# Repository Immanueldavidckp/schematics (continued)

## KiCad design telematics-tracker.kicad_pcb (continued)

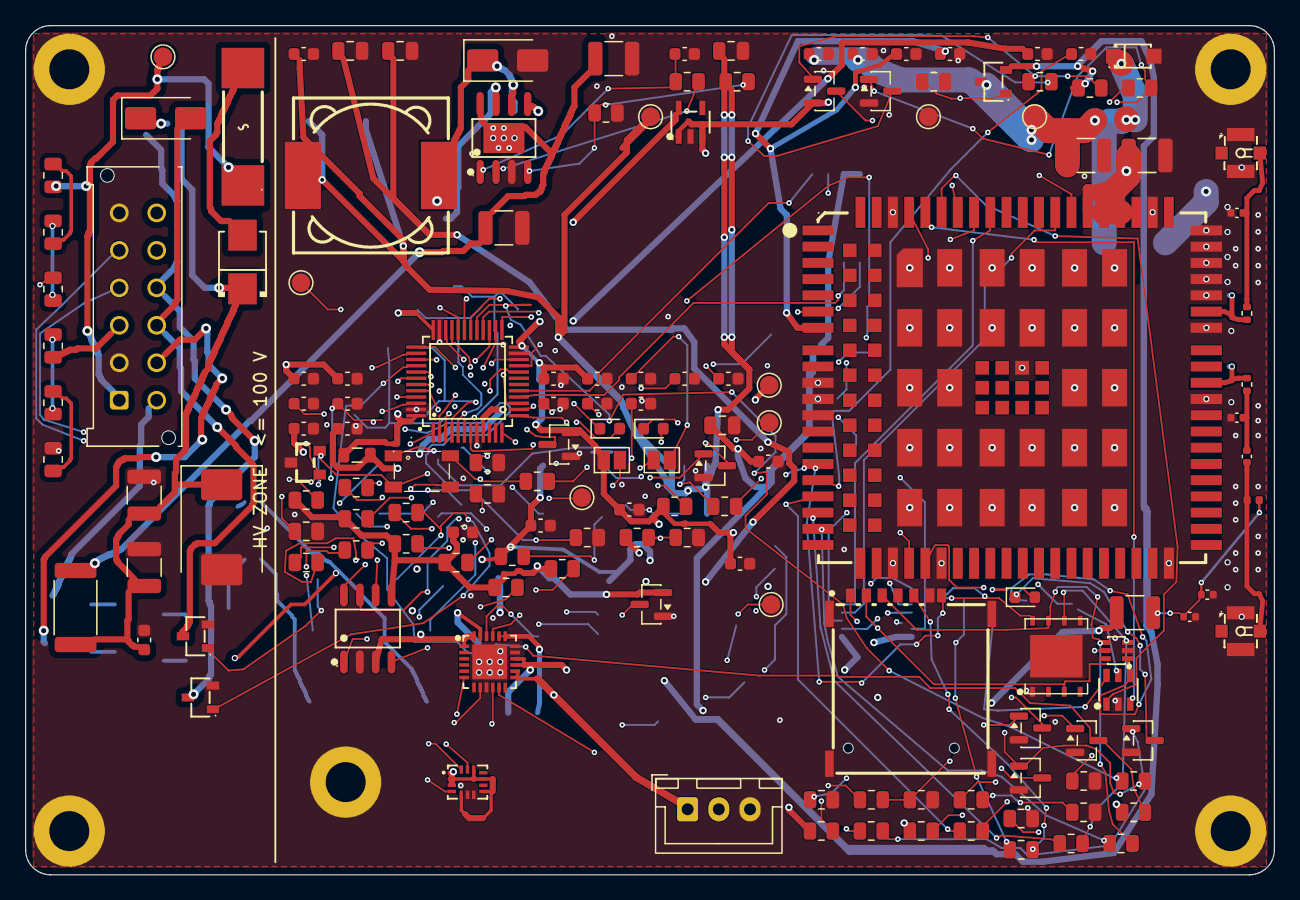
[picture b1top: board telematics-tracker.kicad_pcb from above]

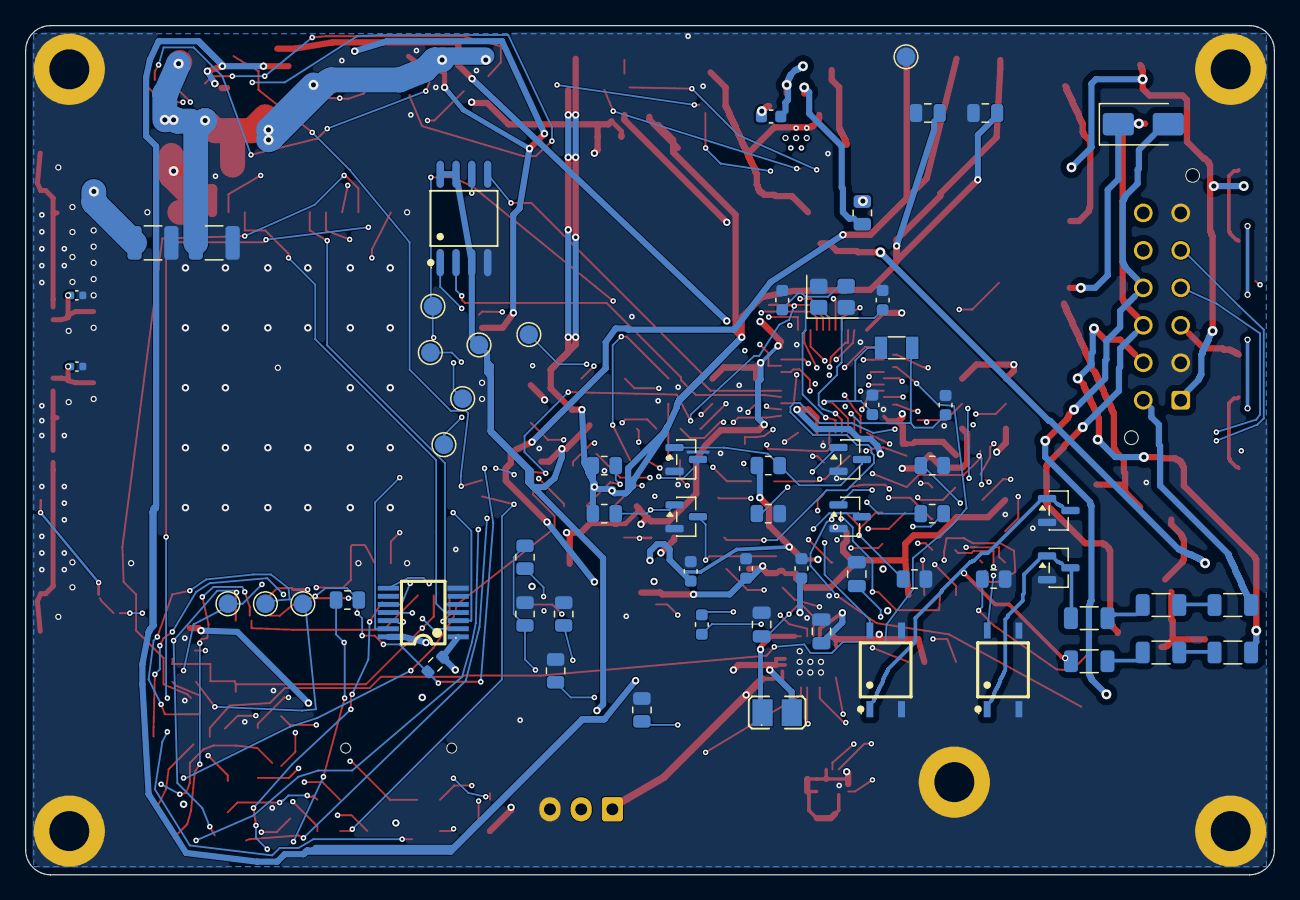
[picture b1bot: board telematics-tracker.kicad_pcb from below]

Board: 4 copper layers, 100.0 x 68.0 mm, 217 parts (64 on the bottom side), 138 nets.

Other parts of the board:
H1, H2, H3, H4, H5: MountingHole_3.2mm_M3_ISO7380_Pad

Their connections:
GND: H1.1, H2.1, H3.1, H4.1, H5.1; also elsewhere on the board

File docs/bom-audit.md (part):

# BOM audit against LCSC part data

Generated by `tools/bom_audit.py` from `out/bom.csv`; stock checked for 10 boards. 77 lines, 185 parts, **0 line(s) to fix**.

| status | designators | value | footprint | LCSC | JLCPCB | manufacturer / MPN | LCSC says | notes |
|---|---|---|---|---|---|---|---|---|
| ok | AF1,AF2 | U.FL | CONN-SMD_XY-IPEX1 | C53133524 | extended 13005 | XYECONN XY-IPEX1 | None | Frequency 6GHz (could not compare 'U.FL') |
| ok | C1,C2 | 18pF | C_0603_1608Metric | C1647 | basic 271351 | Samsung Electro-Mechanics CL10C180JB8NNNC | CAP CER 18pF 50V C0G 0603 | Capacitance 18pF; LCSC retail 0 (JLCPCB 271351 ok) |
| ok | C3,C4 | 6.8pF | C_0603_1608Metric | C318672 | extended 164620 | Samsung Electro-Mechanics CL10C6R8CB8NNNC | CAP CER 6.8pF 50V C0G 0603 | Capacitance 6.8pF |
| ok | C5,C6,C8,C9,C10,C11,C13,C20,C23,C24,C25,C26,C27,C28,C29,C43,C45,C46,C47,C72,C76,C80 | 100nF | C_0603_1608Metric | C14663 | basic 56742618 | YAGEO CC0603KRX7R9BB104 | CAP CER 100nF 50V X7R 0603 | Capacitance 100nF |
| ok | C7,C14,C21,C42,C44,C61,C68,C69,C75 | 1uF | C_0603_1608Metric | C106858 | extended 297295 | YAGEO CC0603KRX7R8BB105 | CAP CER 1uF 25V X7R 0603 | Capacitance 1uF |
| ok | C12,C63 | 4.7uF | C_0805_2012Metric | C354262 | extended 580518 | YAGEO CC0805KKX7R8BB475 | CAP CER 4.7uF 25V X7R 0805 | Capacitance 4.7uF |
| ok | C22 | 4.7nF | C_0603_1608Metric | C1621 | extended 524732 | Samsung Electro-Mechanics CL10B472KB8NNNC | CAP CER 4.7nF 50V X7R 0603 | Capacitance 4.7nF |
| ok | C40,C41,C81,C82 | 47uF X7R | C_1210_3225Metric | C84494 | extended 56966 | muRata GRM32ER71A476KE15L | CAP CER 47uF 10V X7R 1210 | Capacitance 47uF |
| ok | C62,C65,C66,C67,C77,C78,C79 | 10uF | C_0805_2012Metric | C109040 | extended 5453 | muRata GRM21BC71E106KE11L | CAP CER 10uF 25V X7S 0805 | Capacitance 10uF |
| ok | C64 | 47nF | C_0603_1608Metric | C1622 | basic 847982 | Samsung Electro-Mechanics CL10B473KB8NNNC | CAP CER 47nF 50V X7R 0603 | Capacitance 47nF |
| ok | C70,C71,C73,C74 | 2.2uF 100V | C_1210_3225Metric | C5449052 | extended 74114 | CCTC TCC1210X7R225K101MT | CAP CER 2.2uF 100V X7R 1210 | Capacitance 2.2uF |
| ok | C83 | 100nF | C_0402_1005Metric | C1525 | basic 23387840 | Samsung Electro-Mechanics CL05B104KO5NNNC | CAP CER 100nF 16V X7R 0402 | Capacitance 100nF |
| ok | C84 | 100pF C0G | C_0402_1005Metric | C1546 | basic 3404157 | FH 0402CG101J500NT | CAP CER 100pF 50V C0G 0402 | Capacitance 100pF |
| ok | C85 | 10nF | C_0402_1005Metric | C15195 | basic 4230575 | Samsung Electro-Mechanics CL05B103KB5NNNC | CAP CER 10nF 50V X7R 0402 | Capacitance 10nF |
| ok | D1 | S3M | SMB_L4.3-W3.6-LS5.3-RD | C5204901 | extended 23802 | TWGMC S3M | DIODE STANDARD 1kV 3A SMB | part S3M |
| ok | D2 | SMDJ100A | D_SMC | C1977839 | extended 2645 | Littelfuse SMDJ100A | None | part SMDJ100A |
| ok | D3 | PESD1CAN | SOT-23_L2.9-W1.3-P1.90-LS2.4-BR | C15771 | extended 303623 | Nexperia PESD1CAN,215 | ESD DIODE 24VWM 70VC SOT-23 | part PESD1CAN,215 |
| ok | D5,D6 | BAV70 | SOT-23 | C2501 | extended 1577419 | Nexperia BAV70,215 | DIODE ARR GP 100V 215mA SOT-23 | part BAV70,215 |
| ok | D7,D8,D16 | SS3200 | D_SMA | C65001 | extended 105538 | MDD(Microdiode Semiconductor) SS3200 | DIODE SCHOTTKY 200V SMA(DO-214AC) | part SS3200 |
| ok | D10,D11 | BAV99 | SOT-23 | C2500 | basic 1146860 | Nexperia BAV99,215 | DIODE ARR GP 100V 215mA SOT-23 | part BAV99,215 |
| ok | D12 | SMF5.0A | SOD-123FL_L2.7-W1.8-LS3.8-RD | C193402 | extended 575544 | MDD(Microdiode Semiconductor) SMF5.0A | TVS DIODE 5VWM 9.2VC SOD-123FL | part SMF5.0A |
| ok | D13 | NET | LED_0603_1608Metric | C2286 | basic 3829613 | Hubei KENTO Elec KT-0603R | LED RED WATER CLEAR 0603 SMD | LED Red |
| ok | D14 | PESD5V0L5UY | SOT-363_L2.0-W1.3-P0.65-LS2.1-BR | C179747 | extended 852 | Nexperia PESD5V0L5UY,115 | ESD DIODE 5VWM 12VC SOT-363 | part PESD5V0L5UY,115 |
| ok | D15 | USBLC6-2SC6 | SOT-23-6_L2.9-W1.6-P0.95-LS2.8-BL | C7519 | extended 43323 | ST USBLC6-2SC6 | ESD DIODE 5.25VWM 17VC SOT-23-6L | part USBLC6-2SC6 |
| ok | D20 | GRN | LED_0603_1608Metric | C12624 | extended 338944 | Hubei KENTO Elec KT-0603G | LED EMERALD GREEN WATER CLEAR 0603 SMD | LED Emerald Green |
| ok | D21 | BLU | LED_0603_1608Metric | C2288 | extended 51561 | Hubei KENTO Elec KT-0603B | LED BLUE WATER CLEAR 0603 SMD | LED Blue |
| ok | F1 | 1A 250V | FUSE-SMD_L10.1-W3.1 | C95352 | extended 2308 | Littelfuse 0443001.DR | FUSE BRD MNT 1A 250VAC/VDC SMD | rated 1A |
| ok | FB1 | 600R@100MHz | L_0805_2012Metric | C1017 | basic 379892 | Sunlord GZ2012D601TF | -55℃~+125℃ 1 300mΩ 500mA 600Ω@100MHz ±25% 0805 Ferrite Beads ROHS | LCSC lookup refused; JLCPCB record used; 600Ω@100MHz in JLCPCB description; LCSC retail 0 (JLCPCB 379892 ok) |
| ok | J1 | WAFER-MX3.0-12PZZ | XUNPU_MX3.0-12PZZ_2x06_P3.00mm_Vertical | C7588012 | extended 0 | XUNPU WAFER-MX3.0-12PZZ | CONN HEADER TH 12POS 3mm | part WAFER-MX3.0-12PZZ |
| ok | J2 | B3B-XH-A | JST_XH_B3B-XH-A_1x03_P2.50mm_Vertical | C144394 | extended 191996 | JST B3B-XH-A(LF)(SN) | CONN HEADER TH 3POS 2.5mm | part B3B-XH-A(LF)(SN) |
| ok | L1 | 150uH 2.7A | IND-SMD_L12.3-W12.3 | C21325 | extended 3994 | Shun Xiang Nuo SMDRI127-151MT | FIXED IND 150uH 1.42A 280mΩ SMD,12.3x12.3mm | Inductance 150uH |
| ok | L2 | ACT45B-510-2P | IND-SMD_4P-L4.5-W3.2-TL | C76584 | extended 53395 | TDK ACT45B-510-2P-TL003 | CMC 51uH 200mA 2LN 2.8kΩ SMD | part ACT45B-510-2P-TL003 |
| ok | L3 | 2.2uH | L1008 | C391305 | extended 11806 | muRata DFE252012P-2R2M=P2 | FIXED IND 2.2uH 2.2A 70mΩ 1008 | Inductance 2.2uH |
| ok | L4 | 68nH | L_0402_1005Metric | C3221844 | extended 18682 | muRata LQW15AN68NG80D | FIXED IND 68nH 320mA 1.128Ω 0402 | Inductance 68nH |
| ok | OK1,OK2 | EL357N(D) | OPTO-SMD-4_L4.4-W4.1-P2.54-LS7.0-BL | C359074 | extended 20988 | EVERLIGHT EL357N(A)(TA)-VG | DC Input Isolation Voltage (rms)： 3750V | part EL357N(A)(TA)-VG |
| ok | Q1,Q2 | AM2390N-TP | SOT-23-3_L2.9-W1.3-P1.90-LS2.4-BR | C51886143 | extended 1931 | TECH PUBLIC AM2390N-TP | MOSFET 150V 4A SOT-23-3L | part AM2390N-TP |
| ok | Q3 | AO3401A | SOT-23-3_L2.9-W1.3-P1.90-LS2.4-BR | C15127 | basic 826742 | AOS AO3401A | MOSFET P-CH 30V 4A SOT-23 | part AO3401A |
| ok | Q4,Q5,Q6,Q7,Q8,Q9,Q10,Q11,Q12,Q14 | MMBT3904 | SOT-23 | C20526 | basic 277323 | JSCJ MMBT3904(RANGE:100-300) | TRANS NPN 40V 200mA SOT-23 | part MMBT3904(RANGE:100-300); LCSC retail 0 (JLCPCB 277323 ok) |
| ok | Q13 | MMBT3906 | SOT-23 | C75549 | extended 109285 | Nexperia MMBT3906,215 | TRANS PNP 40V 200mA SOT-23 | part MMBT3906,215 |
| ok | R1,R2,R43,R44,R47,R48,R51,R63,R87 | 10k | R_0805_2012Metric | C17414 | basic 50688212 | UNI-ROYAL 0805W8F1002T5E | RES 10kΩ ±1% 125mW 0805 | Resistance 10kΩ |
| ok | R3,R69 | 0R | R_0805_2012Metric | C17477 | basic 6982197 | UNI-ROYAL 0805W8F0000T5E | RES 0Ω ±1% 125mW 0805 | Resistance 0Ω |
| ok | R4,R6 | 330R | R_0805_2012Metric | C17630 | basic 2198180 | UNI-ROYAL 0805W8F3300T5E | RES 330Ω ±1% 125mW 0805 | Resistance 330Ω |
| ok | R5,R42,R46,R53,R55,R57,R59,R64 | 4.7k | R_0805_2012Metric | C17673 | basic 5212697 | UNI-ROYAL 0805W8F4701T5E | RES 4.7kΩ ±1% 125mW 0805 | Resistance 4.7kΩ |
| ok | R7,R8,R45,R49 | 2.2k | R_0805_2012Metric | C17520 | basic 3642650 | UNI-ROYAL 0805W8F2201T5E | RES 2.2kΩ ±1% 125mW 0805 | Resistance 2.2kΩ |
| ok | R11,R12 | 60.4R | R_0805_2012Metric | C228935 | extended 65203 | YAGEO AC0805FR-0760R4L | RES 60.4Ω ±1% 125mW 0805 | Resistance 60.4Ω |
| ok | R14,R15,R16,R17,R18,R19 | 12k | R_1206_3216Metric | C17912 | extended 69452 | UNI-ROYAL 1206W4F1202T5E | RES 12kΩ ±1% 250mW 1206 | Resistance 12kΩ |
| ok | R21,R22 | 220k | R_0805_2012Metric | C17556 | basic 269118 | UNI-ROYAL 0805W8F2203T5E | RES 220kΩ ±1% 125mW 0805 | Resistance 220kΩ |
| ok | R23,R24 | 100R | R_0805_2012Metric | C17408 | basic 9460969 | UNI-ROYAL 0805W8F1000T5E | RES 100Ω ±1% 125mW 0805 | Resistance 100Ω |
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
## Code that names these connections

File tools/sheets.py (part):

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
    sh.text("MCU - AT32F403ACGT7 LQFP-48.  Pin map per telematics-handoff.md section 5.",
            (g(60), g(48)), 2.0)
    sh.text("JTAG must be disabled in firmware (SWD retained) before PA15/PB3/PB4 "
            "are used as GPIO.  CAN1 uses the PB8/PB9 remap.", (g(60), g(52)))

    # --- cross-sheet signals: pin -> (net, shape) -----------------------
    HIER = {
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    sh.net(sj, "1", "3V3", length=g(3))
    sh.net(sj, "2", "BOOT0", length=g(3))

    # --- BOOT1 (PB2) pulldown: required for deterministic boot mode
    sh.series("Device:R", "R2", "10k", (g(240), g(138)), "BOOT1", None,
              R0805, LCSC_R10K, gnd_b=True)

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    sh.hier(bulk, "1", "3V3", "input", length=g(5))
    sh.gnd(bulk, "2", length=g(3))

    # --- heartbeat LED on PC13 (sinks current: 3V3 -> R -> LED -> PC13)
    sh.series("Device:R", "R4", "330R", (g(252), g(150)), "3V3", "SYS_LED_A",
              R0805, LCSC_R330)   # green LED Vf ~2.8 V: 330R -> ~1.5 mA (PC13 sinks <= 3 mA)
    d1 = sh.place("Device:LED", "D20", "GRN", (g(252), g(158)), LED0603, LCSC_LED_GRN)
    sh.net(d1, "2", "SYS_LED_A", length=g(3))
    sh.net(d1, "1", "SYS_LED", length=g(3))

    # --- network-status LED on PB11 via NPN, per section 5
    sh.series("Device:R", "R5", "4.7k", (g(268), g(150)), "NET_STATUS_LED",
              "NSL_BASE", R0805, LCSC_R4K7)
    q1 = sh.place("Transistor_BJT:Q_NPN_BEC", "Q4", "MMBT3904",
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            sh.hier(j1, pin, net, shape, length=g(6))
        else:
            sh.net(j1, pin, net, length=g(6))
    sh.text("J1 pinout: 1 VIN, 2 GND, 3 IGN, 4 CANH, 5 CANL, 6 GND, 7 DI1, "
            "8 DI2, 9 DO1, 10 DO2, 11/12 spare.", (g(20), g(104)))
    # TP8/TP9 on the J1 spares are removed: handoff section 2 rule 8 asks for
    # test points on rails, SWD, both UARTs and CAN - a spare connector pin is
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    sh.net(e1, "5", "USIM_VDD", length=g(4))
    sh.gnd(e1, "2", length=g(3))
    sh.nc(e1, "6")
    # USIM_DET: Quectel Fig 18 pulls it up to VDD_EXT through 51k (the pin has
    # no internal pull-up); the holder's switch shorts it to GND with no card.
    sh.series("Device:R", "R91", "51k", (g(300), g(60)), "VDD_EXT_1V8",
              "USIM_DET", R0603, "C23196")   # UNI-ROYAL 0603WAF5102T5E 1%
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                  (g(134), g(140)), "jlc:L1008", LCSC_L2R2)
    sh.net(l3, "1", "SW_CHG", length=g(4))
    sh.net(l3, "2", "SYS", length=g(4))
    # hier, not net: the power sheet had only LOCAL "SYS" labels, so the
    # charger output (U6/L3/C65-C68/U9) was net /power/SYS and the modem
    # switch Q3/Q13, R38 sense and TP13 sat on an unpowered global SYS.
    # ERC flagged it only as same_local_global_label. Same pattern as 3V3.
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
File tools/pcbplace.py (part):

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    "TP6": (46.0, 26.0, 0, 1),    # 3V3
    "TP7": (29.5, 2.5, 0, 1),     # GND: anywhere over the plane
    # NOT at x 36.5: that is inside the buck cluster (C73 at 38.3) and the
    # SWD test points there walled U5_IS's pin-7 escape (HV 41/42).
    "TP1": (47.0, 29.0, 0, 1),    # SWDIO
    "TP2": (49.0, 27.0, 0, 1),    # SWCLK
    "TP3": (43.5, 21.5, 0, 1),    # NRST
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
    F-20 / SKILL P1: conformal coating is a safety-critical process
    requirement here, not a finish preference. The EG11752's exposed pad is
    VIN_B at up to 100 V with its own signal pins 0.55 mm away, so the board
    only meets creepage once coated. Whoever inspects the assembly has to know
    that this specific area is load-bearing.
    """
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    as approved: 1.5 mm is defence-in-depth for externally-wired nets exposed
    to harness transients and contamination; the buck cluster (U5, L1, D16,
    bootstrap cap, output caps, SW_BUCK / VIN_B / U5_VB) is internal,
    post-TVS/R80, coated, and compact by construction - SW_BUCK cannot be
    1.5 mm from U5's own FB/VCC pins in any package on earth.
    """
    z = pcbnew.ZONE(board)
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
    This is what makes the 1.5 mm HV-to-signal rule expressible. That rule is a
    BOARD-LEVEL zone separation requirement, and it cannot be applied blindly:
    U5's exposed pad carries VIN_B at up to 100 V and its own signal pins sit
    0.55 mm away inside the SOIC-8 package, so no layout can achieve 1.5 mm
    there. Scoping the rule to items inside this area keeps it satisfiable and
    stops it masking genuine violations elsewhere. See design-log F-20.
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                                      pcbnew.ToMM(pd.GetPosition().y), dia))
                        break
    # U5 exposed pad: the skill file requires the buck's thermal pad stitched
    # to L2/L3 with at least 9 vias. EG11752 pin 9 is the EP (and is VIN_B on
    # this part, per the datasheet - so these vias carry VIN_B, not GND).
    u5 = _fp(board, "U5")
    if u5 is not None:
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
